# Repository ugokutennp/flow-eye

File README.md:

# flow-eye
IR Illuminator and Camera Mount for Valve Index DIY Eye Tracker

## Prototype

### Note
 - Designed for OV2640-160°.
 - A rubber ring is used to mount the camera.
 - The part in front of the LED is a visible light filter (acrylic that passes only infrared light). It is attached for appearance.

## Rev1.1

### Note
- Designed for OV2640-130°.
- Select a thickness of 0.8 mm when creating PCBs.
- [Schematic](https://github.com/ugokutennp/flow-eye/blob/main/Rev1.1/Pic/Schematic.png).
- [Other Notes (Japanese)](https://github.com/ugokutennp/flow-eye/blob/main/flow-eye.md).

## Frunk
3D data for the integration of a USB 3.0 2-port hub.
It was created based on the following data   
[Index Hardware](https://github.com/ValveSoftware/IndexHardware)

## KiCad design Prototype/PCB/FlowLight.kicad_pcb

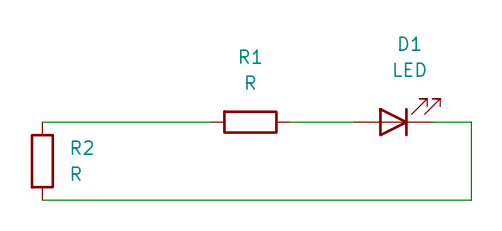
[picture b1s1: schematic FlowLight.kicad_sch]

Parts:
D1: LED; LED_1206_3216Metric_Pad1.42x1.75mm_HandSolder
R1: R; R_0603_1608Metric
R2: R; R_2816_7142Metric

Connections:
unnamed: D1.1 (K), R2.2
unnamed: D1.2 (A), R1.1
unnamed: R1.2, R2.1

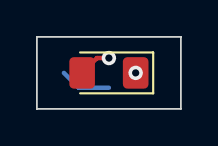
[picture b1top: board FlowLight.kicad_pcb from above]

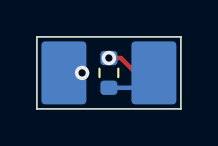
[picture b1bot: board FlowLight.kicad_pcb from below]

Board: 2 copper layers, 8.0 x 4.0 mm, 3 parts (2 on the bottom side), 3 nets.

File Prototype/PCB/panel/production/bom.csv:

Designator,Footprint,Quantity,Value,LCSC Part #
"D1_24, D1_23, D1_22, D1_21, D1_20, D1_19, D1_18, D1_17, D1_16, D1_15, D1_14, D1_13, D1_12, D1_11, D1_10, D1_9, D1_8, D1_7, D1_6, D1_5, D1_4, D1_3, D1_2, D1",1206,24,LED,
"R1_24, R1_23, R1_22, R1_21, R1_20, R1_19, R1_18, R1_17, R1_16, R1_15, R1_14, R1_13, R1_12, R1_11, R1_10, R1_9, R1_8, R1_7, R1_6, R1_5, R1_4, R1_3, R1_2, R1",0603,24,R,
"R2_24, R2_23, R2_22, R2_21, R2_20, R2_19, R2_18, R2_17, R2_16, R2_15, R2_14, R2_13, R2_12, R2_11, R2_10, R2_9, R2_8, R2_7, R2_6, R2_5, R2_4, R2_3, R2_2, R2",2816,24,R,

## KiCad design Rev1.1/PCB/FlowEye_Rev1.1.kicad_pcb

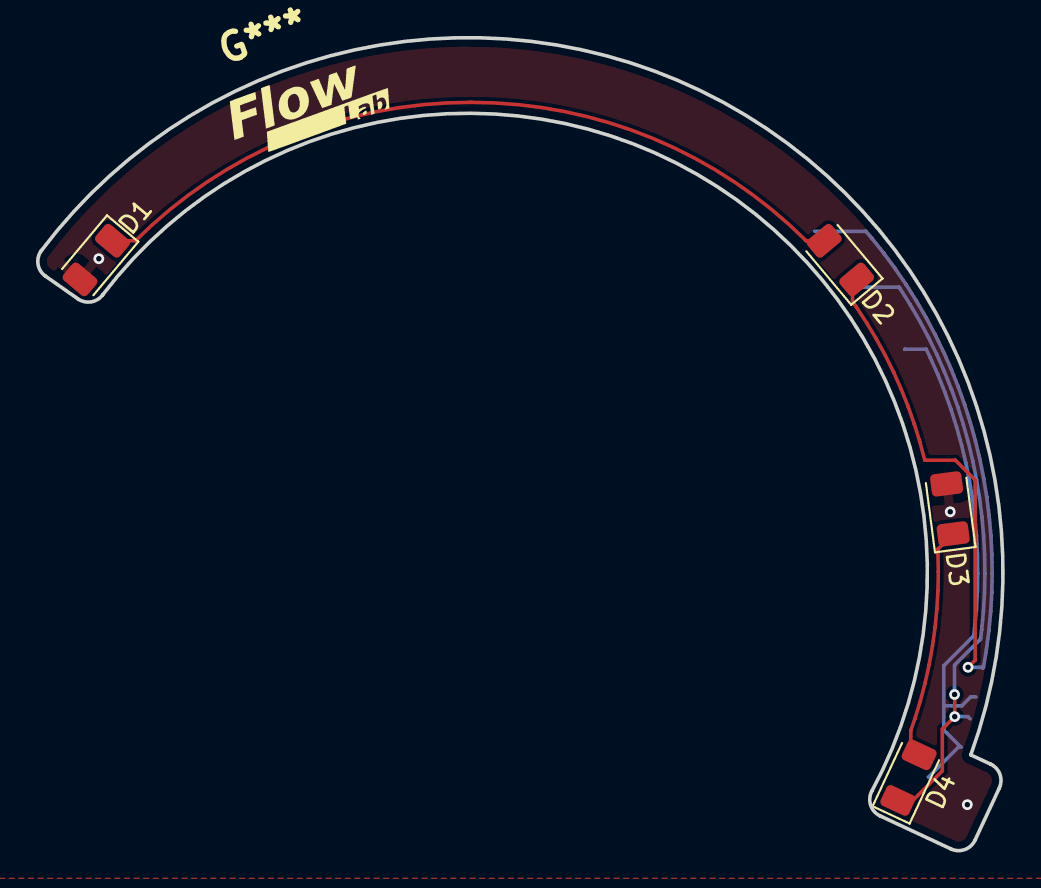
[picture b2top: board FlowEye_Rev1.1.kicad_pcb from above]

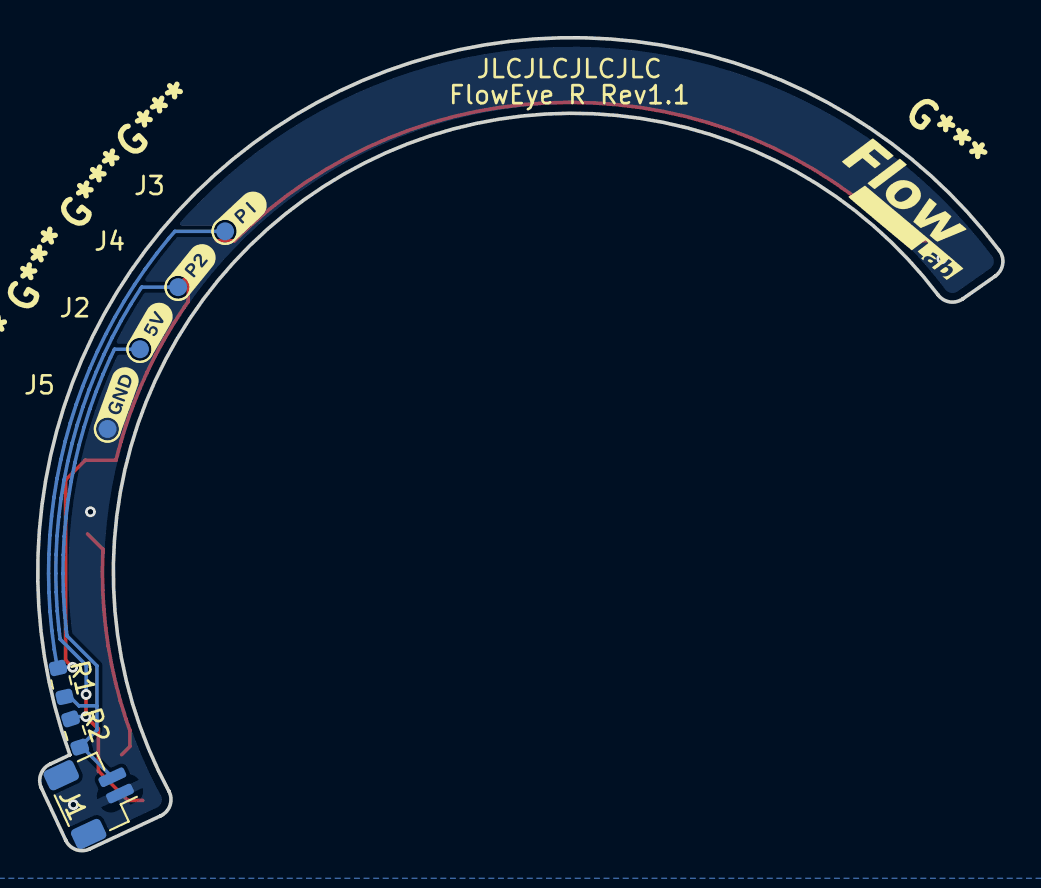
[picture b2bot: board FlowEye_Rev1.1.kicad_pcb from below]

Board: 2 copper layers, 53.6 x 45.2 mm, 11 parts (7 on the bottom side), 6 nets.

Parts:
D1, D2, D3, D4: LED; LED_1206_3216Metric
J1: Conn_01x02; JST_SH_BM02B-SRSS-TB_1x02-1MP_P1.00mm_Vertical
J2: Pad1; TestPoint_Pad_D1.0mm
J3: Pad2; TestPoint_Pad_D1.0mm
J4, J5: Pad3; TestPoint_Pad_D1.0mm
R1, R2: 680R; R_0603_1608Metric

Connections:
+5V: J1.2, J2.1, R1.1, R2.1
GND: D1.2 (A), D3.2 (A), J1.1, J5.1
unnamed: D2.1 (K), J3.1, R1.2
unnamed: D1.1 (K), D2.2 (A)
unnamed: D4.1 (K), J4.1, R2.2
unnamed: D3.1 (K), D4.2 (A)

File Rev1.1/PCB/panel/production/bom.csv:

Designator,Footprint,Quantity,Value,LCSC Part #
"D1, D2, D3, D4",1206,4,LED,
J1,JST_SH_BM02B-SRSS-TB_1x02-1MP_P1.00mm_Vertical,1,Conn_01x02,
J2,TestPoint_Pad_D1.0mm,1,Pad1,
J3,TestPoint_Pad_D1.0mm,1,Pad2,
"J4, J5",TestPoint_Pad_D1.0mm,2,Pad3,
"R1, R2",0603,2,680R,

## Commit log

2024-03-05 Create LICENSE
2024-03-05 Upload Prototype data
2024-03-05 Add pic
2024-04-09 Add V1 Render Pic
2024-04-26 Add Rev1.1
2024-08-31 Add Frunk
2024-08-31 Add clinp
